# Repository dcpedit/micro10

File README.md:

# µ10 Keyboard

Here you will find all the source files I used to build my µ10 (aka Micro10) keyboard.  Below is a list of features:

* 10u wide QAZ-ish layout
* Supports a 10u spacebar
* Designed to be wireless (via nice!nano + ZMK)
* Optional daughterboard for OLED and rotary encoder
* PCB uses Kailh hot swap sockets
* PCB supports a 1.25u modifier on each end if a split spacebar (2.25u + 2.75u) setup or 6.25u spacebar is utilized.  This will require modifications to the case design (mainly to add blockers).

[Keyboard Layout Editor (KLE)](http://www.keyboard-layout-editor.com/#/gists/2a9c0bfd3bc5586766325f682a7adc31)

# ZMK Firmware

See my fork of ZMK under the `dcpedit` branch:
https://github.com/dcpedit/zmk/tree/dcpedit

The relevant files are in the `micro10` folder under shields:
https://github.com/dcpedit/zmk/tree/dcpedit/app/boards/shields/micro10

```
git clone -b dcpedit https://github.com/dcpedit/zmk.git
```

## Build
Follow the [ZMK environment setup](https://zmk.dev/docs/development/setup).  I highly recommend using VS Code & Docker.
```
cd app
west build -b nice_nano_v2 -- -DSHIELD=micro10
```
Binary will be located here.  Copy it into your nice!nano:
```
app/build/zephyr/zmk.uf2
```

# Image Gallery
https://imgur.com/a/AuKd2NT

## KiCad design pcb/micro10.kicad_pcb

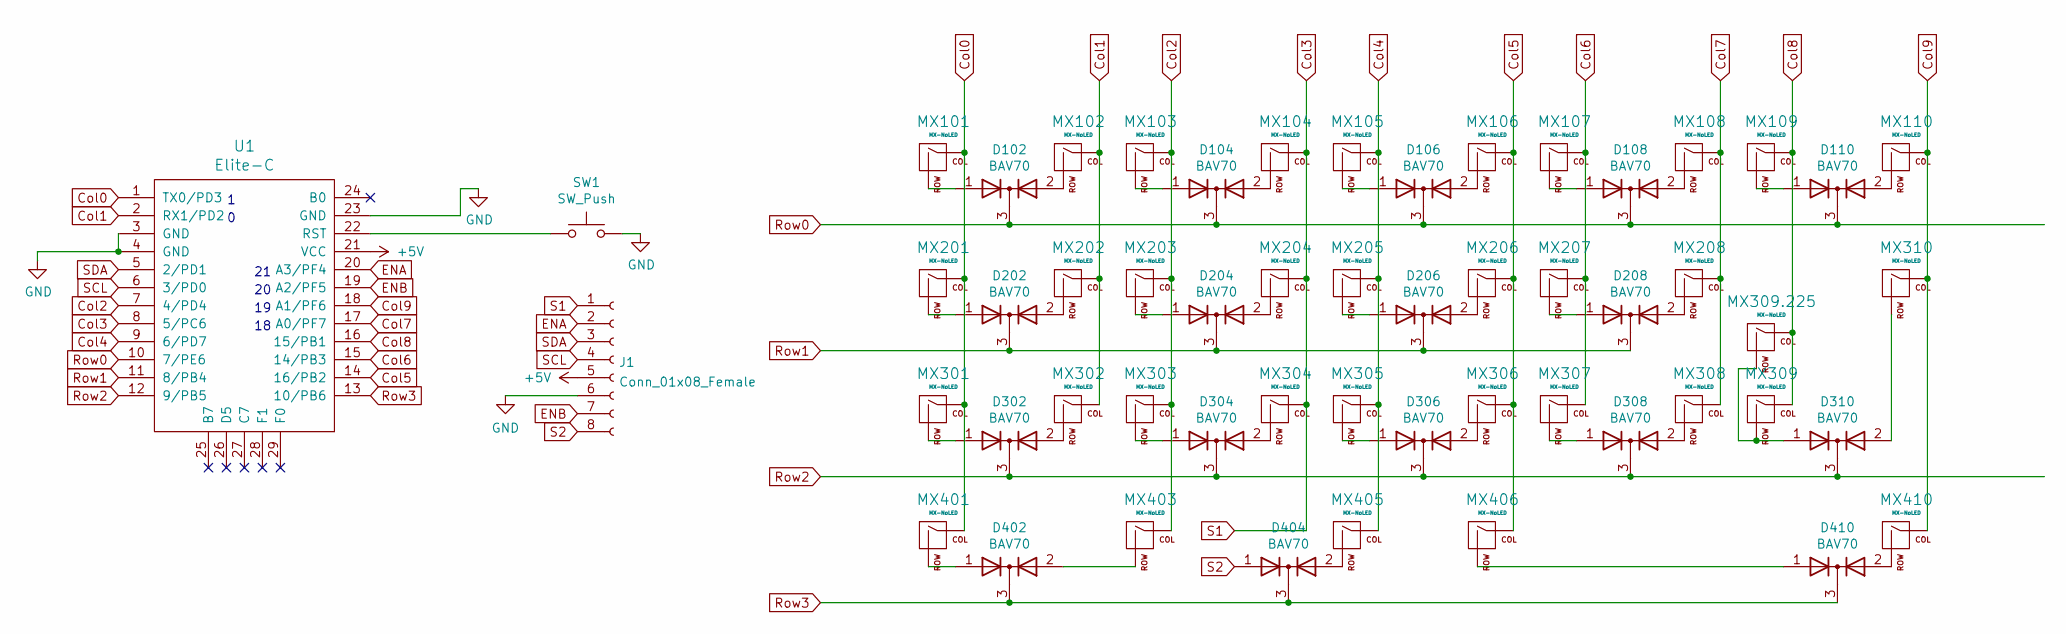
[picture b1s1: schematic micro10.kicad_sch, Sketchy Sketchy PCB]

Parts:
D102, D104, D106, D108, D110, D202, D204, D206, D208, D302, D304, D306, D308, D310, D402, D404, D410: BAV70; SOT-23_Handsoldering
J1: Conn_01x08_Female
MX101, MX102, MX103, MX104, MX105, MX106, MX107, MX108, MX109, MX110, MX202, MX203, MX204, MX205, MX206, MX207, MX208, MX302, MX303, MX304, MX305, MX306, MX307, MX308, MX309, MX309.225, MX310, MX403, MX405, MX406, MX410: MX-NoLED; MXOnly-1U-Hotswap
MX201: MX-NoLED; MXOnly-1.5U-Hotswap
MX301: MX-NoLED; MXOnly-1.75U-Hotswap
MX401: MX-NoLED; MXOnly-2.25U-Hotswap
SW1: SW_Push; SW_Tactile_SPST_Angled_MJTP1117
U1: Elite-C

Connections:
+5V: J1.5, U1.21 (VCC)
Col0: MX101.1 (COL), MX201.1 (COL), MX301.1 (COL), MX401.1 (COL), U1.1 (TX0/PD3)
Col1: MX102.1 (COL), MX202.1 (COL), MX302.1 (COL), U1.2 (RX1/PD2)
Col2: MX103.1 (COL), MX203.1 (COL), MX303.1 (COL), MX403.1 (COL), U1.7 (4/PD4)
Col3: J1.1, MX104.1 (COL), MX204.1 (COL), MX304.1 (COL), U1.8 (5/PC6)
Col4: MX105.1 (COL), MX205.1 (COL), MX305.1 (COL), MX405.1 (COL), U1.9 (6/PD7)
Col5: MX106.1 (COL), MX206.1 (COL), MX306.1 (COL), MX406.1 (COL), U1.14 (16/PB2)
Col6: MX107.1 (COL), MX207.1 (COL), MX307.1 (COL), U1.15 (14/PB3)
Col7: MX108.1 (COL), MX208.1 (COL), MX308.1 (COL), U1.17 (A0/PF7)
Col8: MX109.1 (COL), MX309.1 (COL), MX309.225.1 (COL), U1.16 (15/PB1)
Col9: MX110.1 (COL), MX310.1 (COL), MX410.1 (COL), U1.18 (A1/PF6)
ENA: J1.2, U1.20 (A3/PF4)
ENB: J1.7, U1.19 (A2/PF5)
GND: J1.6, SW1.2, U1.3 (GND), U1.4 (GND), U1.23 (GND)
unnamed: D102.1 (A), MX101.2 (ROW)
unnamed: D102.2 (A), MX102.2 (ROW)
unnamed: D104.1 (A), MX103.2 (ROW)
unnamed: D104.2 (A), MX104.2 (ROW)
unnamed: D106.1 (A), MX105.2 (ROW)
unnamed: D106.2 (A), MX106.2 (ROW)
unnamed: D108.1 (A), MX107.2 (ROW)
unnamed: D108.2 (A), MX108.2 (ROW)
unnamed: D110.1 (A), MX109.2 (ROW)
unnamed: D110.2 (A), MX110.2 (ROW)
unnamed: D202.1 (A), MX201.2 (ROW)
unnamed: D202.2 (A), MX202.2 (ROW)
unnamed: D204.1 (A), MX203.2 (ROW)
unnamed: D204.2 (A), MX204.2 (ROW)
unnamed: D206.1 (A), MX205.2 (ROW)
unnamed: D206.2 (A), MX206.2 (ROW)
unnamed: D208.1 (A), MX207.2 (ROW)
unnamed: D208.2 (A), MX208.2 (ROW)
unnamed: D302.1 (A), MX301.2 (ROW)
unnamed: D302.2 (A), MX302.2 (ROW)
unnamed: D304.1 (A), MX303.2 (ROW)
unnamed: D304.2 (A), MX304.2 (ROW)
unnamed: D306.1 (A), MX305.2 (ROW)
unnamed: D306.2 (A), MX306.2 (ROW)
unnamed: D308.1 (A), MX307.2 (ROW)
unnamed: D308.2 (A), MX308.2 (ROW)
unnamed: D310.1 (A), MX309.2 (ROW), MX309.225.2 (ROW)
unnamed: D310.2 (A), MX310.2 (ROW)
unnamed: D402.1 (A), MX401.2 (ROW)
unnamed: D402.2 (A), MX403.2 (ROW)
unnamed: D404.2 (A), MX405.2 (ROW)
unnamed: D410.1 (A), MX406.2 (ROW)
unnamed: D410.2 (A), MX410.2 (ROW)
unnamed: SW1.1, U1.22 (RST)
Row0: D102.3 (K), D104.3 (K), D106.3 (K), D108.3 (K), D110.3 (K), U1.10 (7/PE6)
Row1: D202.3 (K), D204.3 (K), D206.3 (K), D208.3 (K), U1.11 (8/PB4)
Row2: D302.3 (K), D304.3 (K), D306.3 (K), D308.3 (K), D310.3 (K), U1.12 (9/PB5)
Row3: D402.3 (K), D404.3 (K), D410.3 (K), U1.13 (10/PB6)
S2: D404.1 (A), J1.8
SCL: J1.4, U1.6 (3/PD0)
SDA: J1.3, U1.5 (2/PD1)

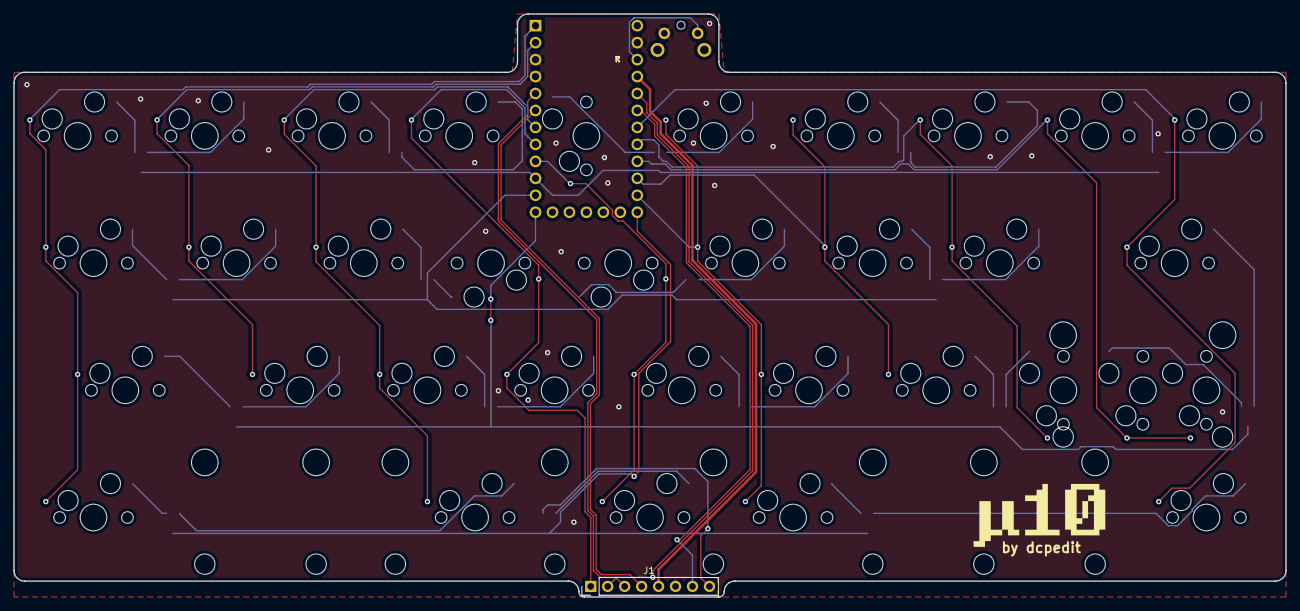
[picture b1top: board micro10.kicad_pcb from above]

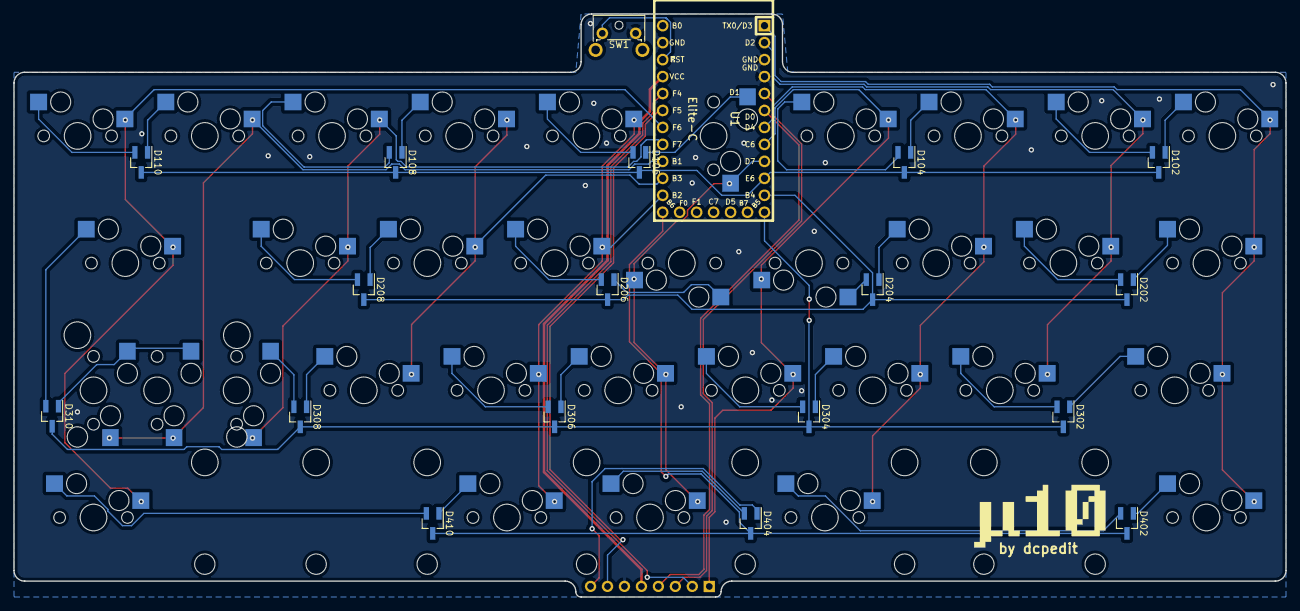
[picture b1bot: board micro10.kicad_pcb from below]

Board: 2 copper layers, 190.5 x 87.3 mm, 54 parts (18 on the bottom side), 55 nets.

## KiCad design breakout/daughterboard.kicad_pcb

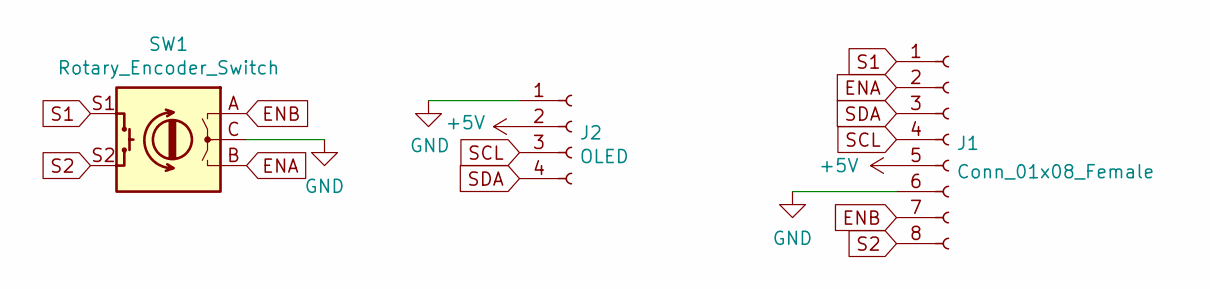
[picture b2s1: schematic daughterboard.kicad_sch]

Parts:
J1: Conn_01x08_Female; PinHeader_1x08_P2.54mm_Vertical
J2: OLED; SSD1306_OLED
SW1: Rotary_Encoder_Switch; RotaryEncoder_Alps_EC11E-Switch_Vertical_H20mm

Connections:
+5V: J1.5, J2.2
ENA: J1.2, SW1.B
ENB: J1.7, SW1.A
GND: J1.6, J2.1, SW1.C
S1: J1.1, SW1.S1
S2: J1.8, SW1.S2
SCL: J1.4, J2.3
SDA: J1.3, J2.4

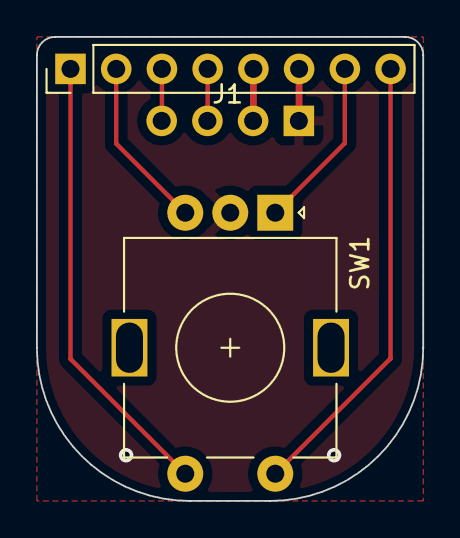
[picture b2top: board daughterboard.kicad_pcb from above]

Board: 2 copper layers, 21.5 x 25.8 mm, 3 parts (0 on the bottom side), 8 nets.

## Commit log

2022-04-10 Case files
2022-05-14 Add readme
2022-05-14 Remove outdated gerbers
2022-05-14 Fix typos
2022-05-14 Clarify readme
2022-05-14 Add license file
2022-05-14 Add build details
2022-05-14 Add firmware binary
